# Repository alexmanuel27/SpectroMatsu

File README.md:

# SpectroMatsu

A lightweight, portable, open-source spectrophotometer designed for in-situ water quality and other compound analysis. Built with the Hamamatsu C12880MA miniature spectrometer sensor and the 3-channel ultraviolet AS7331 light sensor.

## Table of Contents

- [Features](#features)
- [Hardware](#hardware)
  - [Sensor](#sensor)
  - [Microcontroller & Display](#microcontroller--display)
  - [Hardware Design (PCB)](#hardware-design-pcb)
- [Software](#software)
- [Installation](#installation)
- [Usage](#usage)
- [License](#license)

## Features

*   **Portable & Low-Cost:** Designed for field use with a focus on affordability.
*   **Open Source:** Hardware schematics and software are freely available.
*   **Real-Time Data:** Captures and displays absorbance spectra.
*   **Local Data Storage:** Saves measurement samples to an external EEPROM.
*   **WiFi Connectivity:** Enables a local web interface for data access and control.
*   **Intuitive Touch Interface:** Easy-to-use graphical menu system on a 1.9" color display.
*   **Sample Management:** Functions to take, save, list, and download sample data (individually or in bulk) via the local web interface.

## Hardware

### Sensor

*   **Model:** 
    *   Hamamatsu C12880MA (340–850 nm, 288 pixels)
    *   AS7331
*   **Type:** Combined miniature linear image sensor for spectral analysis and optical filters with the AS7331 sensor to achieve a broader spectral range.
*   **Spectral Range:** A combination of visible and ultraviolet light, suitable for detecting various water quality indicators through absorbance measurements.
*   **Integration:** Interfaces directly with the custom-designed PCB for signal conditioning and data acquisition.

### Microcontroller & Display

*   **Microcontroller:** ESP32-S3 (specifically, the LilyGo T-Display-S3 module).
*   **Features:** WiFi capability, sufficient processing power for basic spectroscopic calculations.
*   **Display:** 1.9" 320x170 pixel color TFT LCD with capacitive touch panel.
*   **Purpose:** Provides the user interface for control, data visualization (spectra), and menu navigation.

### Hardware Design (PCB)

*   **Status:** Custom-designed PCB specifically for integrating the Hamamatsu C12880MA sensor with the LilyGo T-Display-S3.

*   **Functionality:**
    *   Includes the necessary components for sensor biasing, timing, and signal conditioning (e.g., amplification, filtering).
    *   Interfaces with the LilyGo T-Display-S3's GPIO pins for data acquisition and control.
    *   Provides stable mechanical mounting for the sensor relative to the optical path.

## Software

*   **Platform:** PlatformIO.
*   **Core Functionality:**
    *   Processes raw sensor data to generate absorbance spectra.
    *   Provides a graphical user interface (GUI) on the TFT display using a state machine architecture.
    *   Handles touch input for navigation and control.
    *   Stores measurement data (samples) on an external EEPROM of the ESP32.
    *   Manages WiFi access point (AP) mode.
    *   Runs a local web server providing a web interface for sample listing and downloading (CSV format).
    *   Implements a simple menu system accessible via the touchscreen.

### Key Functionalities

#### Sample Taking:

*   Navigate to the main screen.
*   Press the "REFER" button.
    *   The system saves the blank/reference value for later absorbance calculation.
*   Press the "SAMPLE" button.
    *   The system enters an acquisition and absorbance calculation phase.
*   After acquisition, the resulting spectrum is displayed.
*   Press the "SAVE" button to store the spectrum in the EEPROM with a generated name.

#### Sample Listing:

*   Access the main menu (hamburger icon).
*   Select "SAMPLES".
*   A list of saved sample names and dates (default date shown) is displayed on the screen.

#### Local Web Interface:

*   Activate the WiFi AP by pressing the WiFi button on the main screen.
*   Connect your mobile device or computer to the `SpectroMatsu` WiFi network.
*   Open a web browser and navigate to the AP's IP address (typically `192.168.4.1`).
*   View the list of saved samples.
*   Download individual sample data as CSV files.
*   Download all stored samples as a single CSV file.
*   Turn off the WiFi AP from the web interface.

#### Settings & Info:

*   Access system information (firmware version, device model, WiFi status, sample count) via the "SETTINGS" menu.
*   Use the "ABOUT" menu to view a QR code linking to this repository.

## Installation

1.  Clone or download this repository.
2.  Install [PlatformIO](https://platformio.org/) in your preferred IDE (VSCode recommended).
3.  Open the project folder in PlatformIO.
4.  Ensure your LilyGo T-Display-S3 is connected to your computer via USB.
5.  Build and upload the firmware using PlatformIO's upload command (`Ctrl+Alt+U` in VSCode).

## Usage

1.  Power on the device.
2.  Use the touch screen to navigate menus and take samples.
3.  Activate WiFi via the main screen button to access the web interface.
4.  Connect to the `SpectroMatsu` WiFi network and use a web browser to manage samples.

## License

This project is licensed under the MIT License.

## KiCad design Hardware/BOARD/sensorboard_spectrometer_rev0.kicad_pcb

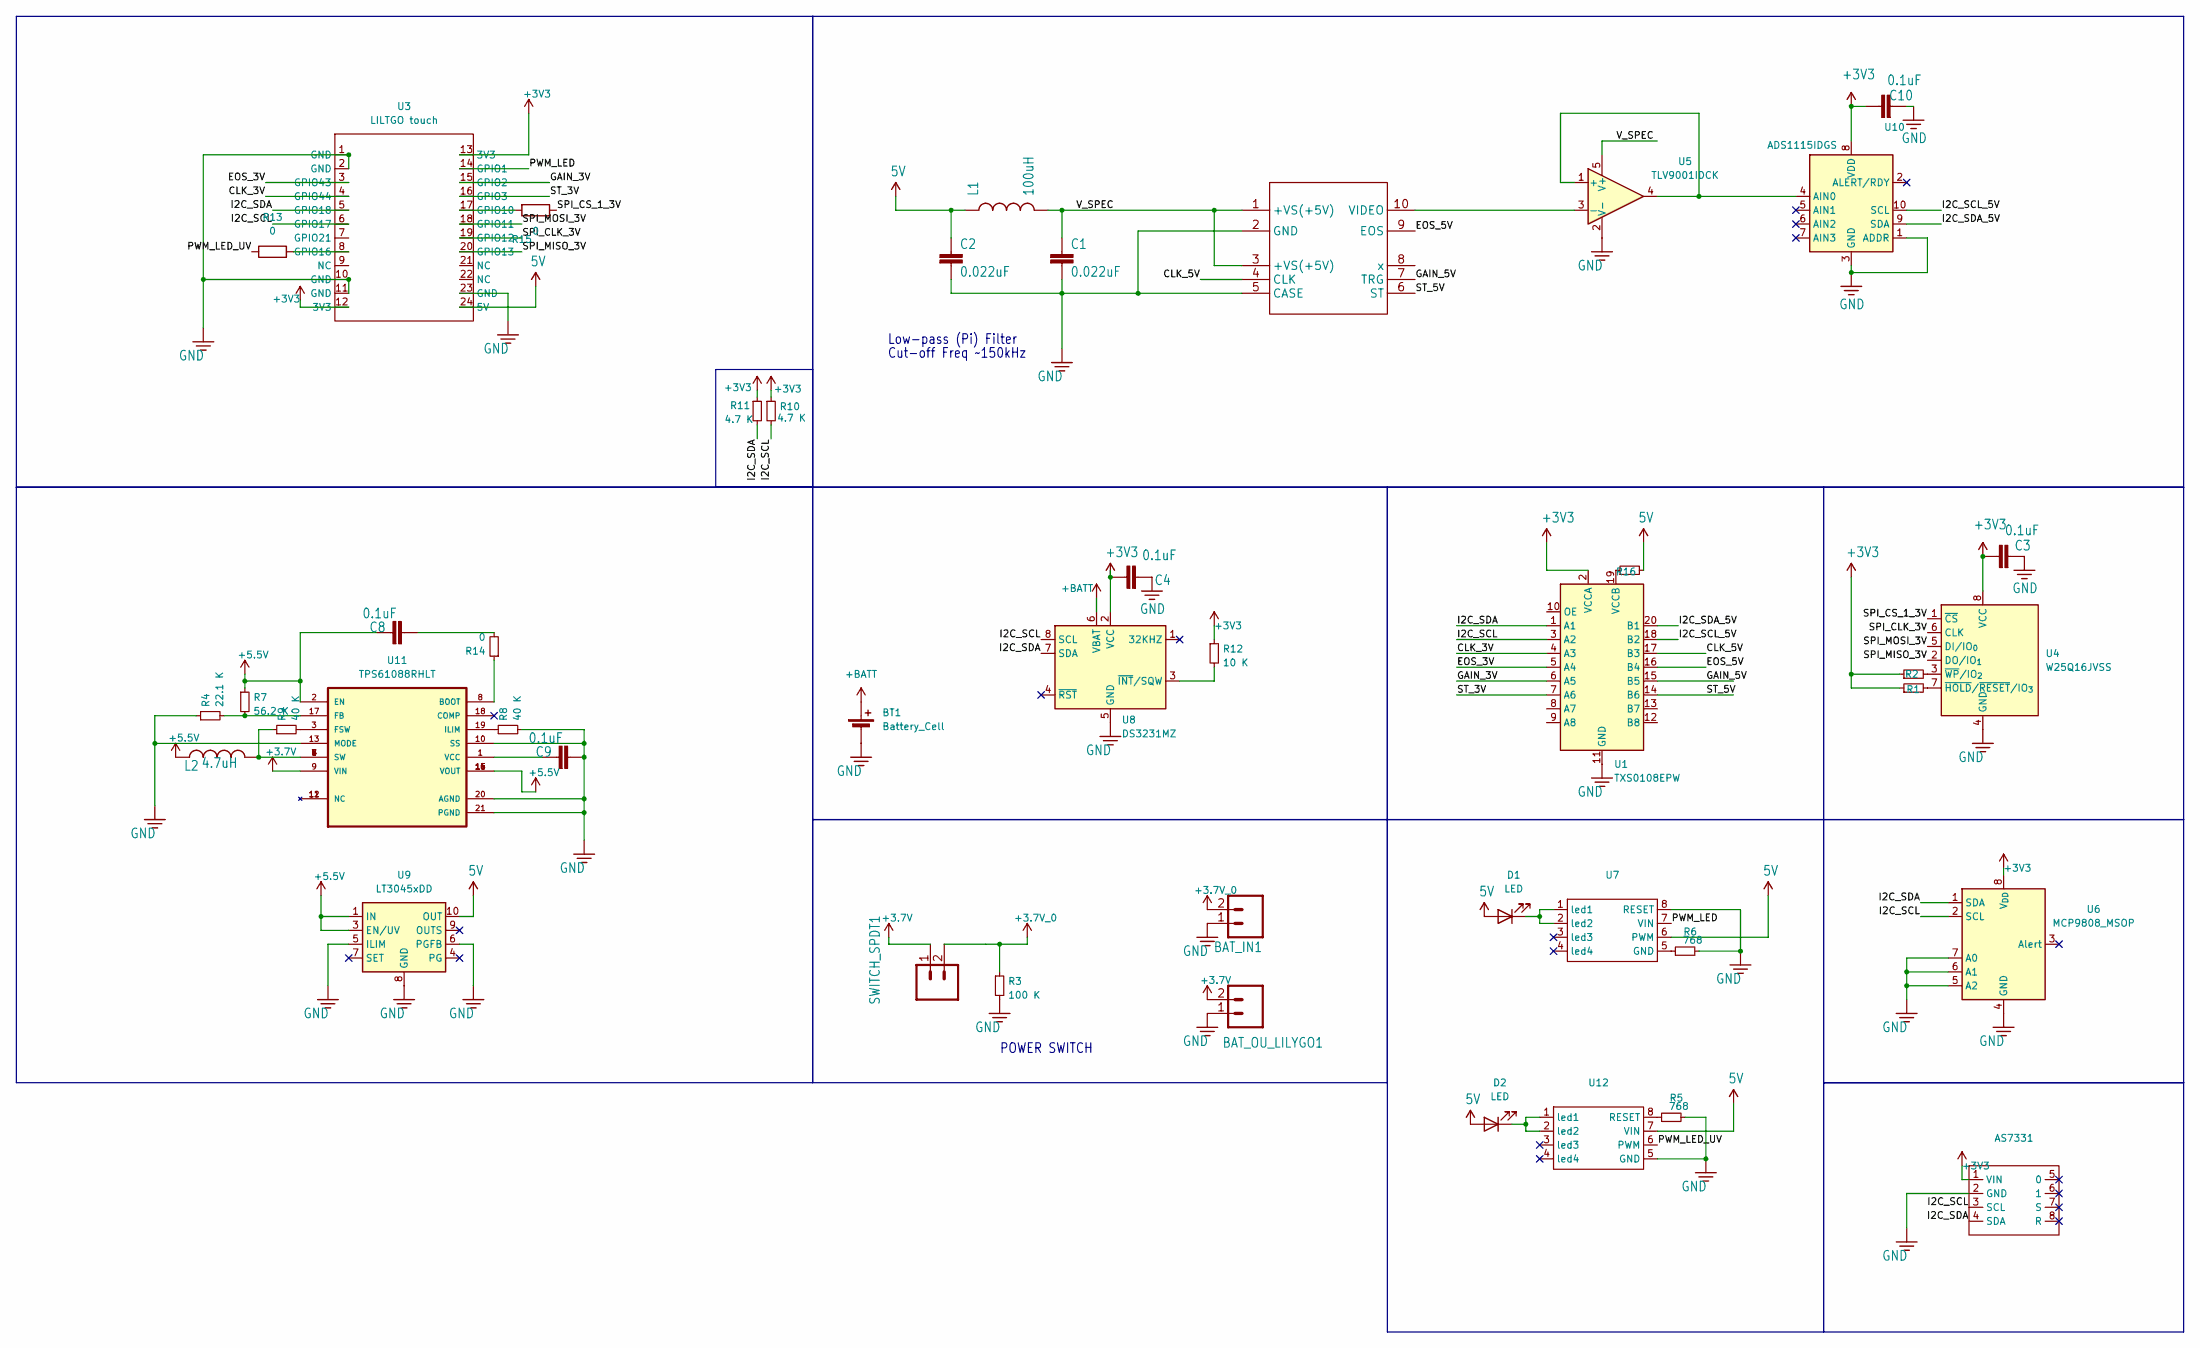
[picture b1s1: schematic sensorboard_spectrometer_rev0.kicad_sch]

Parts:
AS7331: as7331_SMD
BAT_IN1: M02-JST-2MM-SMT; JST_EH_S2B-EH_1x02_P2.50mm_Horizontal
BAT_OU_LILYGO1: M02-JST-2MM-SMT; JST_EH_S2B-EH_1x02_P2.50mm_Horizontal
BT1: Battery_Cell; BatteryHolder_MYOUNG_BS-07-A1BJ001_CR2032
C1, C2: 0.022uF; C_0603_1608Metric
C3: 0.1uF; C_1206_3216Metric
C4, C8, C9, C10: 0.1uF; C_0603_1608Metric
D1, D2: LED; JST_EH_S2B-EH_1x02_P2.50mm_Horizontal
L1: 100uH; L_0603_1608Metric
L2: 4.7uH; L_0603_1608Metric
R1, R12: 10 K; R_0603_1608Metric; LCSC C25804
R2: 10 K; R_1206_3216Metric; LCSC C25804
R3: 100 K; R_0603_1608Metric; LCSC C25804
R4: 22.1 K; R_0603_1608Metric; LCSC C25804
R5, R6: 768; R_0603_1608Metric; LCSC C25804
R7: 56.2 K; R_0603_1608Metric; LCSC C25804
R8, R9: 40 K; R_0603_1608Metric; LCSC C25804
R10: 4.7 K; R_0603_1608Metric; LCSC C25804
R11: 4.7 K; R_1206_3216Metric; LCSC C25804
R13, R15: 0; R_1206_3216Metric
R14: 0; R_0603_1608Metric; LCSC C25804
R16: 0; R_1206_3216Metric; LCSC C25804
SWITCH_SPDT1: M02-JST-2MM-SMT; JST_EH_S2B-EH_1x02_P2.50mm_Horizontal
U1: TXS0108EPW; TSSOP-20_4.4x6.5mm_P0.65mm
U2: C12880MA_SMD
U3: LILTGO touch; Untitled
U4: W25Q16JVSS; SOIC-8_5.3x5.3mm_P1.27mm
U5: TLV9001IDCK; SOT-353_SC-70-5
U6: MCP9808_MSOP; MSOP-8_3x3mm_P0.65mm
U7, U12: PowerIntegrations_SO-8
U8: DS3231MZ; SOIC-8_3.9x4.9mm_P1.27mm; LCSC C107410
U9: LT3045xDD; DFN-10-1EP_3x3mm_P0.5mm_EP1.65x2.38mm
U10: ADS1115IDGS; TSSOP-10_3x3mm_P0.5mm
U11: TPS61088RHLT; IC_MSP430FR2522IRHLR; PARTREV August 2021

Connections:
5V: C2.1, D1.2 (A), D2.2 (A), L1.1, R16.2, U3.24 (5V), U7.6 (PWM), U9.10 (OUT), U12.7 (VIN)
+3.7V: BAT_OU_LILYGO1.2 (1), SWITCH_SPDT1.1 (2), U11.9 (VIN)
+3.7V_0: BAT_IN1.2 (1), R3.1, SWITCH_SPDT1.2 (1)
+3V3: AS7331.1 (VIN), C3.1, C4.1, C10.1, R1.1, R2.1, R10.1, R11.1, R12.1, U1.2 (VCCA), U3.12 (3V3), U3.13 (3V3), U4.8 (VCC), U6.8 (V_{DD}), U8.2 (VCC), U10.8 (VDD)
+5.5V: C8.1, L2.1, R7.1, U9.1 (IN), U9.2 (IN), U9.3 (EN/UV), U11.2 (EN), U11.14 (VOUT), U11.15 (VOUT), U11.16 (VOUT)
+BATT: BT1.1 (+), U8.6 (VBAT)
/CLK_3V: U1.4 (A3), U3.4 (GPIO44)
/CLK_5V: U1.17 (B3), U2.4 (CLK)
/EOS_3V: U1.5 (A4), U3.3 (GPIO43)
/EOS_5V: U1.16 (B4), U2.9 (EOS)
/GAIN_3V: U1.6 (A5), U3.15 (GPIO2)
/GAIN_5V: U1.15 (B5), U2.7 (TRG)
/I2C_SCL: AS7331.3 (SCL), R10.2, U1.3 (A2), U3.6 (GPIO17), U6.2 (SCL), U8.8 (SCL)
/I2C_SCL_5V: U1.18 (B2), U10.10 (SCL)
/I2C_SDA: AS7331.4 (SDA), R11.2, U1.1 (A1), U3.5 (GPIO18), U6.1 (SDA), U8.7 (SDA)
/I2C_SDA_5V: U1.20 (B1), U10.9 (SDA)
/PWM_LED: U3.14 (GPIO1), U7.7 (VIN)
/PWM_LED_UV: R13.1, U12.6 (PWM)
/SPI_CLK_3V: U3.19 (GPIO12), U4.6 (CLK)
/SPI_CS_1_3V: R15.1, U4.1 (~CS)
/SPI_MISO_3V: U3.20 (GPIO13), U4.2 (DO/IO_{1})
/SPI_MOSI_3V: U3.18 (GPIO11), U4.5 (DI/IO_{0})
/ST_3V: U1.7 (A6), U3.16 (GPIO3)
/ST_5V: U1.14 (B6), U2.6 (ST)
/V_SPEC: C1.1, L1.2, U2.1 (+VS(+5V)), U2.3 (+VS(+5V)), U5.5 (V+)
GND: AS7331.2 (GND), BAT_IN1.1 (2), BAT_OU_LILYGO1.1 (2), BT1.2 (-), C1.2, C2.2, C3.2, C4.2, C9.2, C10.2, R3.2, R4.1, R5.2, R6.2, R8.2, U1.11 (GND), U2.2 (GND), U2.5 (CASE), U3.1 (GND), U3.2 (GND), U3.10 (GND), U3.11 (GND), U3.23 (GND), U4.4 (GND), U5.2 (V-), U6.4 (GND), U6.5 (A2), U6.6 (A1), U6.7 (A0), U7.8 (RESET), U8.5 (GND), U9.5 (ILIM), U9.6 (PGFB), U9.8 (GND), U9.11 (GND), U10.1 (ADDR), U10.3 (GND), U11.10 (SS), U11.13 (MODE), U11.20 (AGND), U11.21 (PGND), U12.5 (GND)
unnamed: C8.2, R14.2
unnamed: D1.1 (K), U7.1 (led1), U7.2 (led2)
unnamed: D2.1 (K), U12.1 (led1), U12.2 (led2)
unnamed: L2.2, R9.1, U11.4 (SW), U11.5 (SW), U11.6 (SW), U11.7 (SW)
unnamed: R16.1, U1.19 (VCCB)
unnamed: U2.10 (VIDEO), U5.3 (-)
unnamed: R15.2, U3.17 (GPIO10)
unnamed: R13.2, U3.8 (GPIO16)
unnamed: R1.2, U4.7 (~HOLD/~RESET/IO_{3})
unnamed: R2.2, U4.3 (~WP/IO_{2})
unnamed: R6.1, U7.5 (GND)
unnamed: R12.2, U8.3 (~INT/SQW)
unnamed: U5.1 (+), U5.4, U10.4 (AIN0)
unnamed: R14.1, U11.8 (BOOT)
unnamed: R4.2, R7.2, U11.17 (FB)
unnamed: R9.2, U11.3 (FSW)
unnamed: R8.1, U11.19 (ILIM)
unnamed: C9.1, U11.1 (VCC)
unnamed: R5.1, U12.8 (RESET)

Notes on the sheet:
Low-pass (Pi) Filter
POWER SWITCH
Cut-off Freq ~150kHz

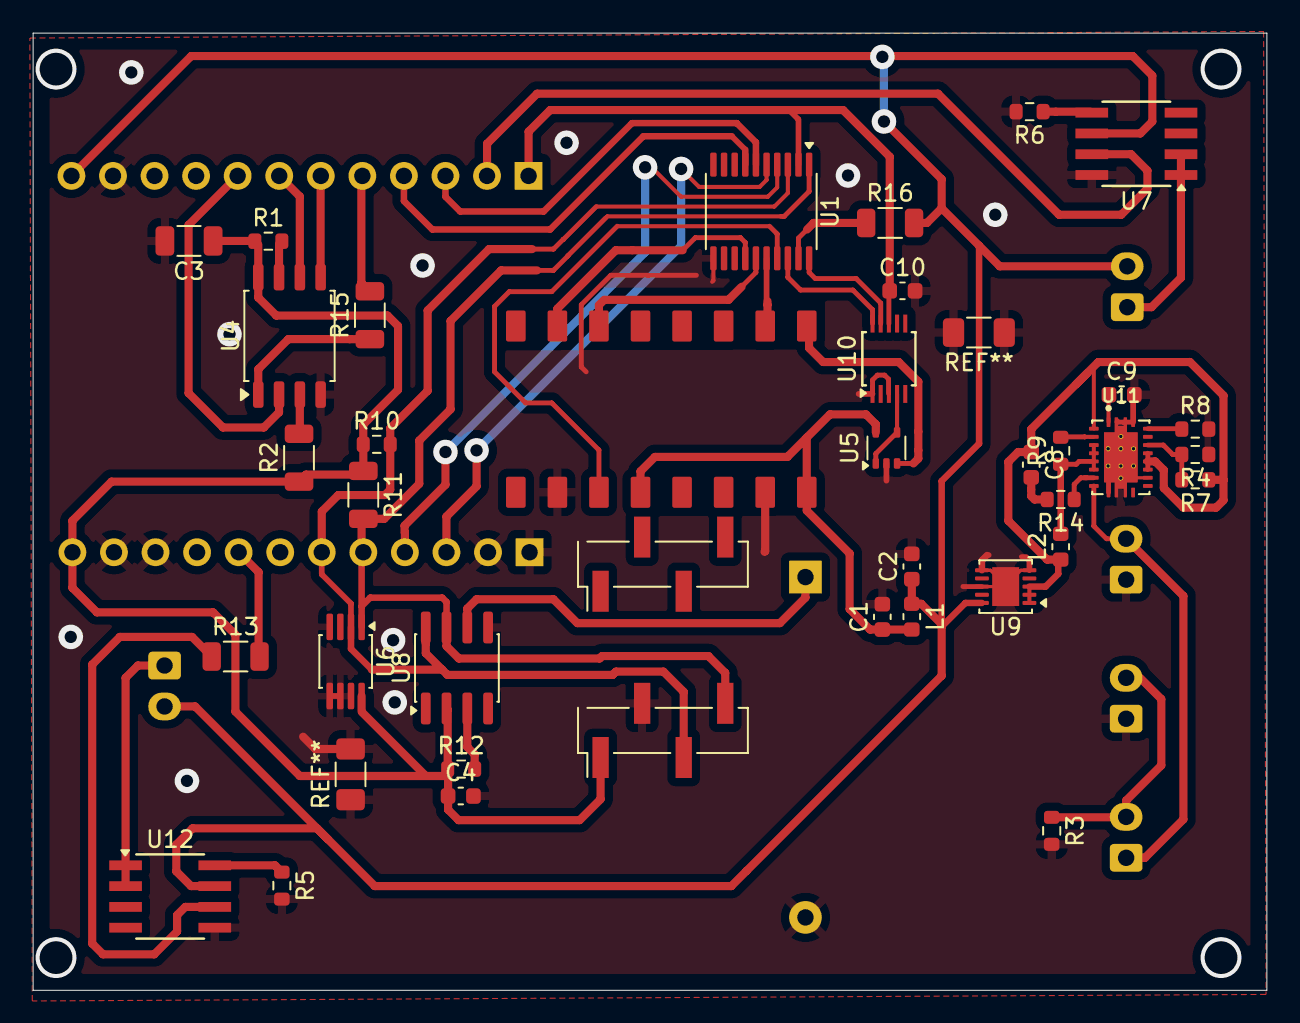
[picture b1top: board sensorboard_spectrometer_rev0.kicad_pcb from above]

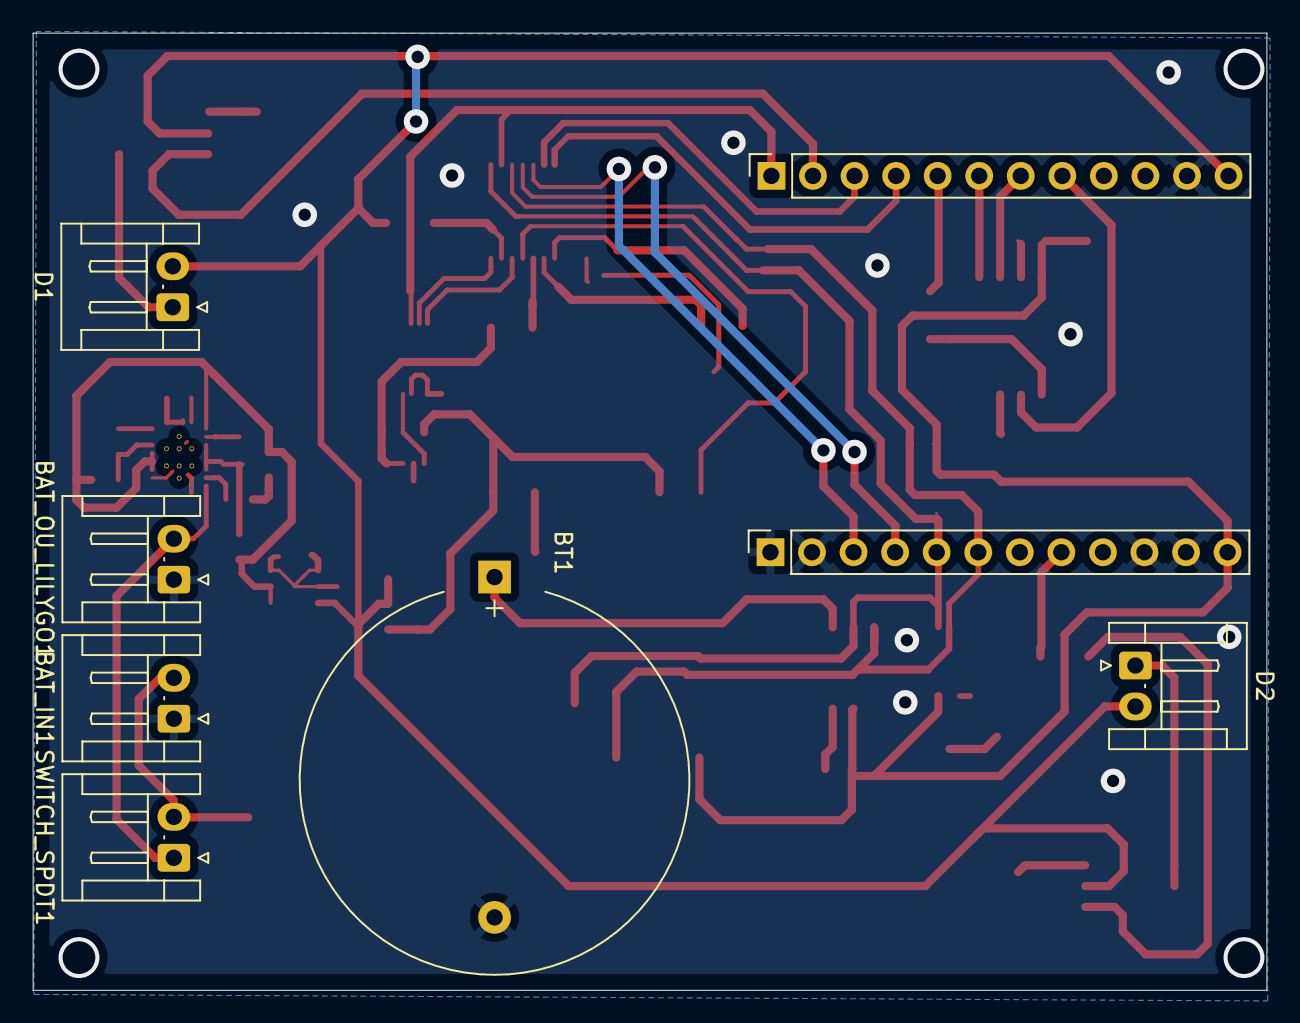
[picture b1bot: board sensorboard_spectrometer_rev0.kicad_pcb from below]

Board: 2 copper layers, 75.4 x 58.5 mm, 44 parts (7 on the bottom side), 45 nets.

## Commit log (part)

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2025-11-04 I created the hardware and placed the first components
2025-11-07 Add Lilygo and the rest of the components
2025-11-21 firmware
2025-11-21 new pcb with the as7331(uv sensor)
2025-11-22 readme
2025-11-22 readme (1000)
2025-12-12 before maked
2025-12-12 alex suggest changes
2025-12-13 not shot resistors
2025-12-16 alex suggest changes again...
2025-12-16 a little bit distance
